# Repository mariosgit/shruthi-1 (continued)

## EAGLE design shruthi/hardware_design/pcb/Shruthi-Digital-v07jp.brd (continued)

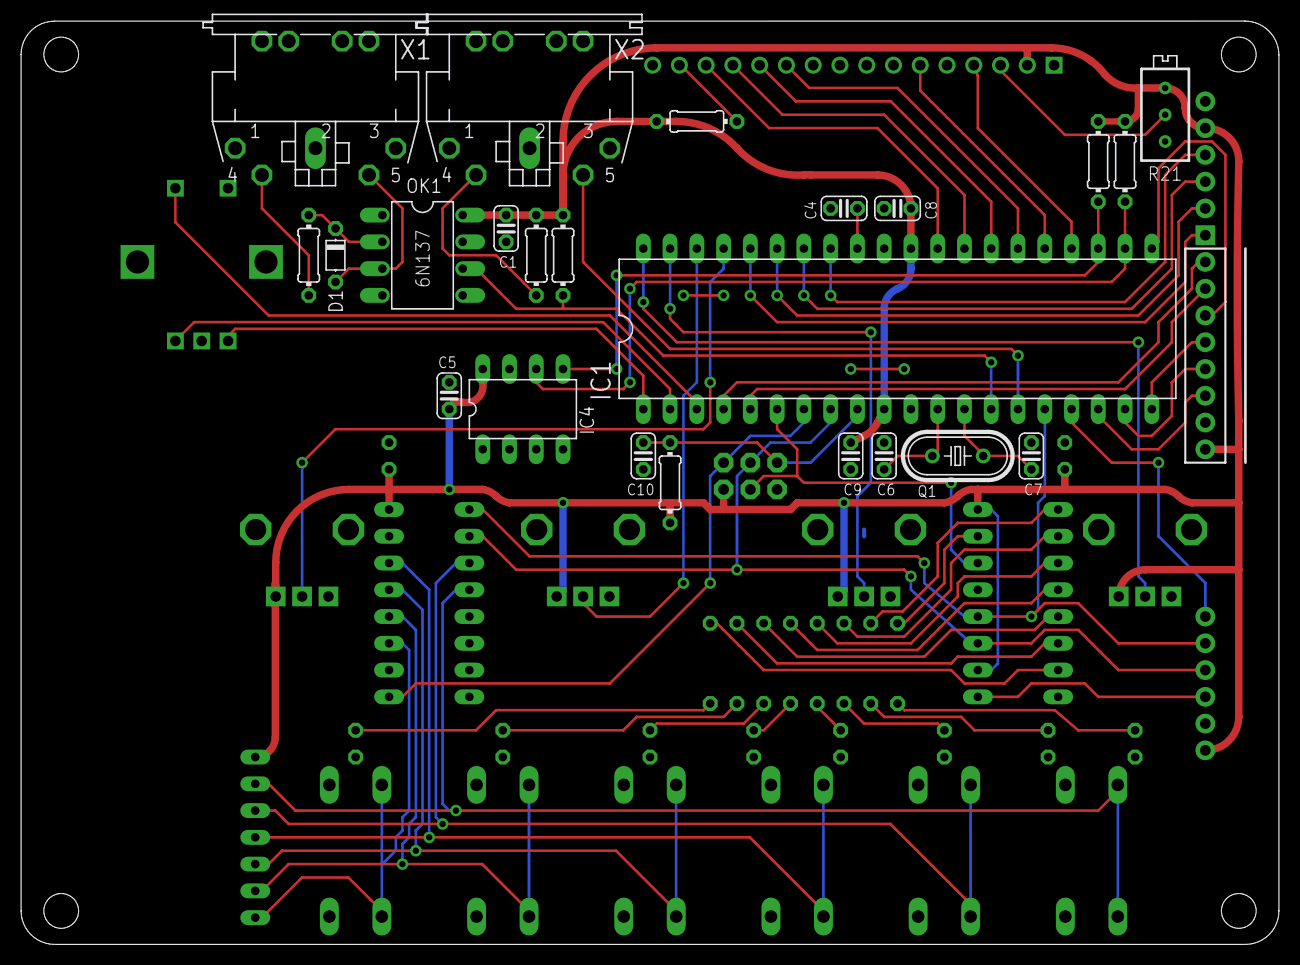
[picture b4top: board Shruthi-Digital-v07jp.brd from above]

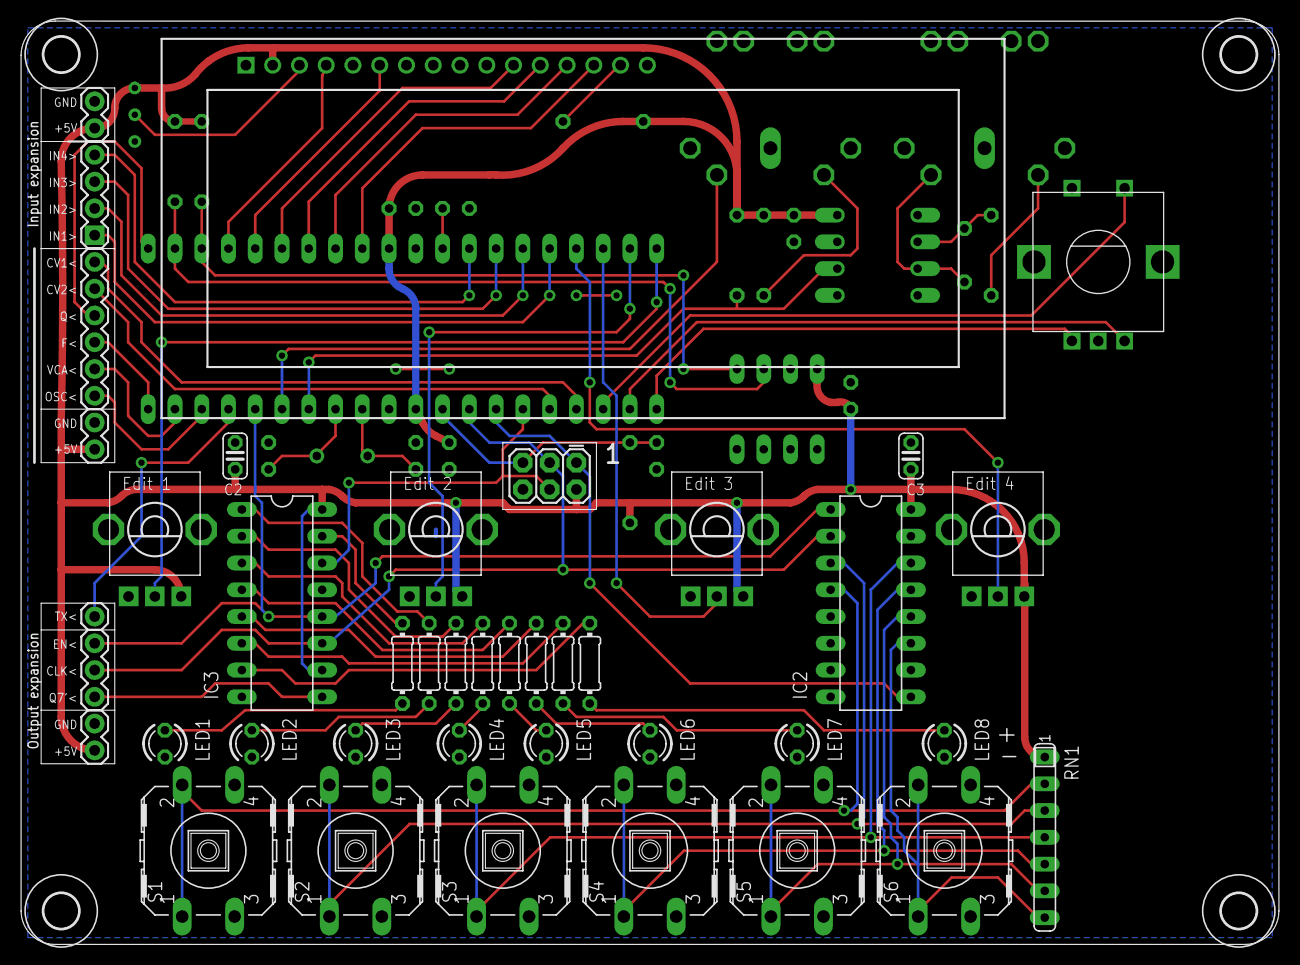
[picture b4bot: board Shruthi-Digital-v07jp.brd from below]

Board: 2 copper layers, 119.4 x 87.6 mm, 70 parts (46 on the bottom side), 67 nets.

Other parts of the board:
U$2, U$3, U$4, U$5: 3,3
U$6: MANGA_GIRL
U$7: MUTABLE_PROF

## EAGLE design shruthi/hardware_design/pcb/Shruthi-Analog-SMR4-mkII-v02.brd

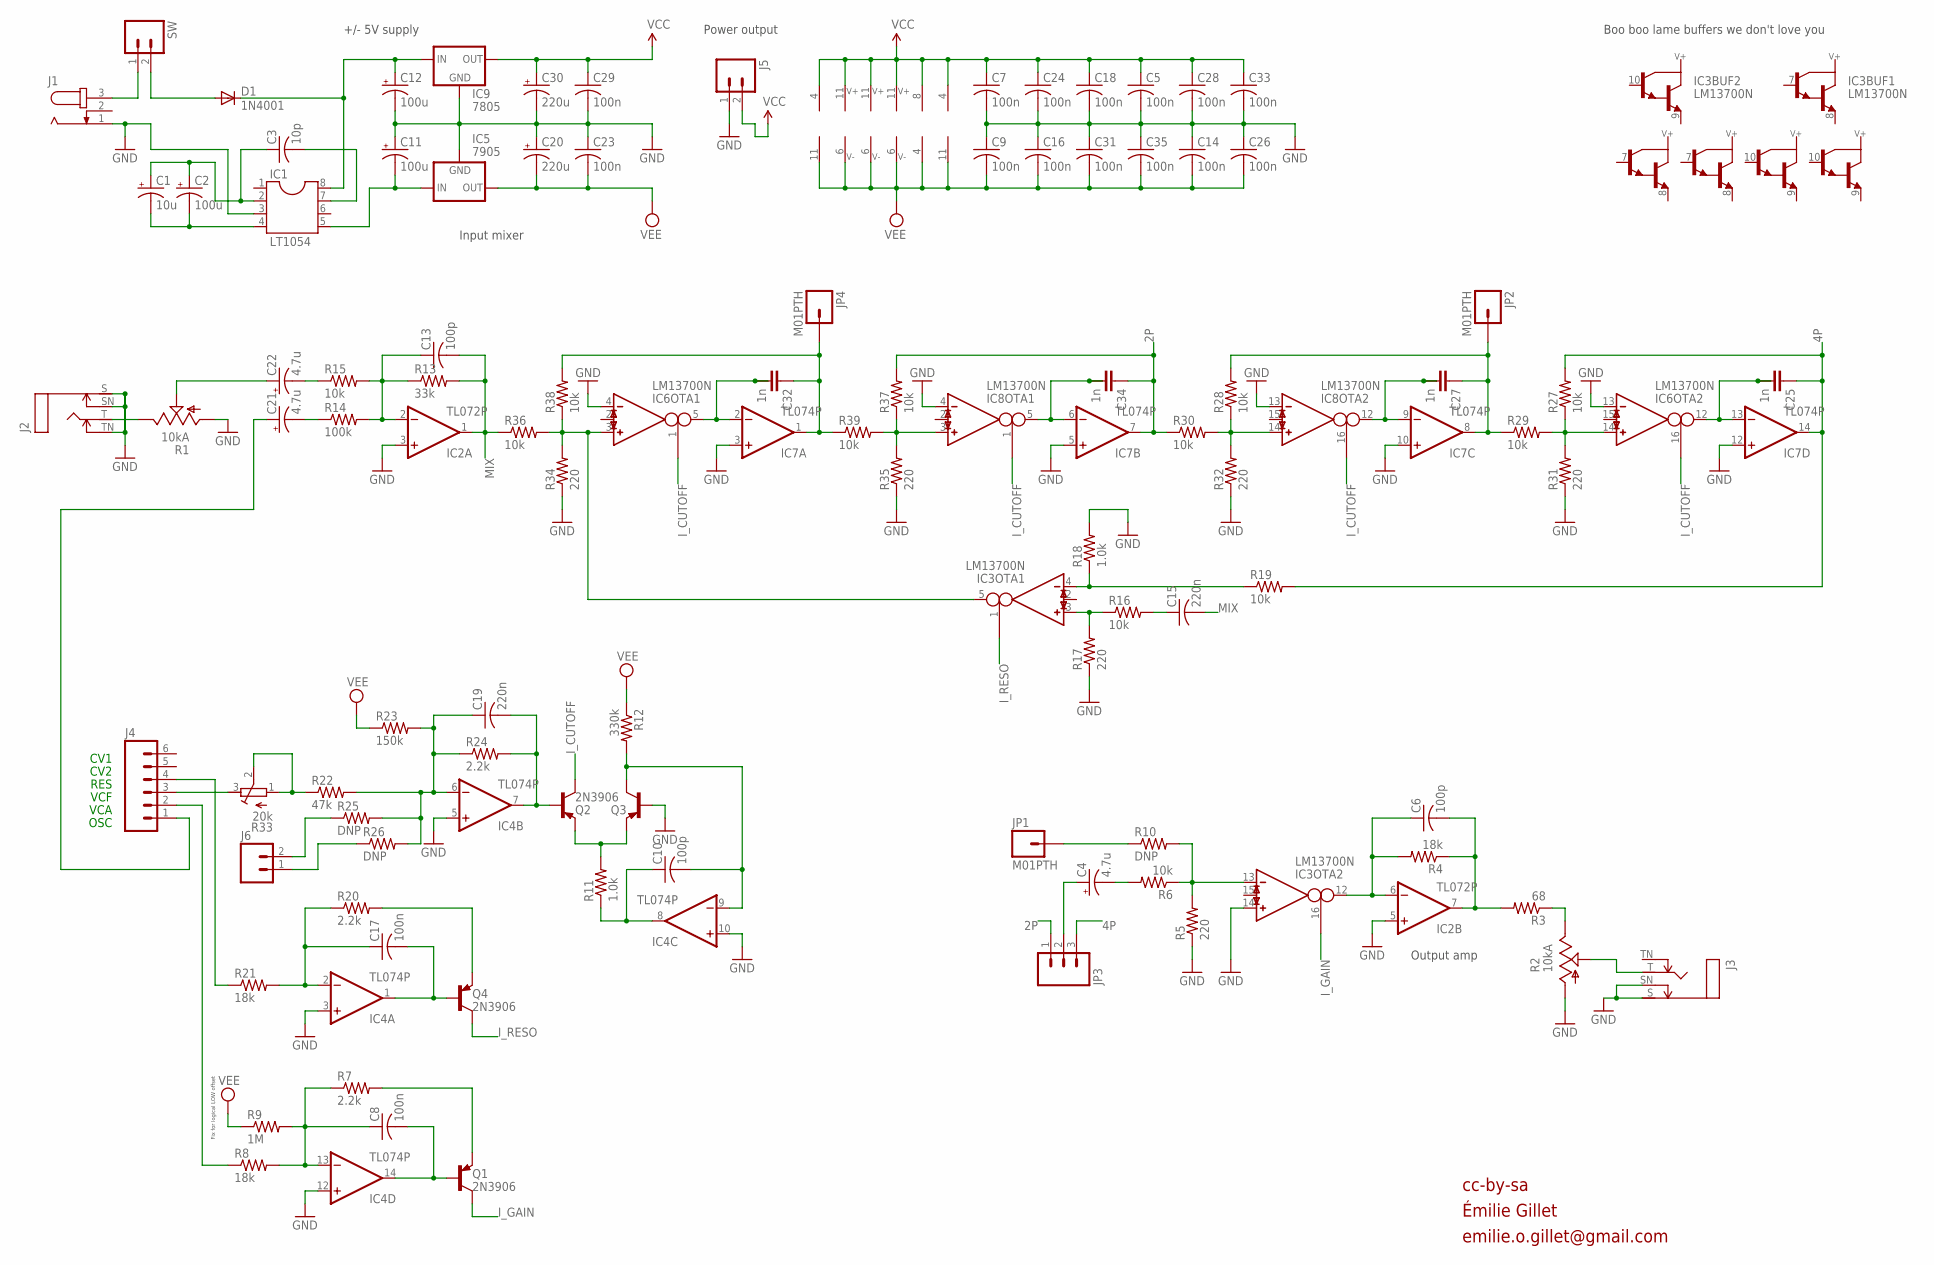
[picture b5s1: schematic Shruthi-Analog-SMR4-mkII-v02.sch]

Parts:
C1: 10u; E2,5-5
C2: 100u; E2,5-6
C3: 10p; C025-025X050
C4, C21, C22: 4.7u; E2,5-6
C5, C7, C8, C9, C14, C16, C17, C18, C23, C24, C26, C28, C29, C31, C33, C35: 100n; C025-025X050
C6, C10, C13: 100p; C025-025X050
C11, C12: 100u; E2,5-7
C15, C19: 220n; C025-025X050
C20, C30: 220u; E5-10,5
C25, C27, C32, C34: 1n; C2.5/5-2
D1: 1N4001; DO41-10
IC1: LT1054; DIL08
IC2: TL072P; DIL08
IC3, IC6, IC8: LM13700N; DIL16
IC4, IC7: TL074P; DIL14
IC5: 7905; 79XXS
IC9: 7805; 78XXS
J1: JACK-PLUG2; SPC4078_BIG_HOLES
J2, J3: MONOSWS; NMJ4HC-S
J4: M06SIP; 1X06
J5, J6: M02PTH; 1X02
JP1, JP2, JP4: M01PTH; 1X01
JP3: M03PTH; 1X03
Q1, Q2, Q3, Q4: 2N3906; TO92-
R1, R2: 10kA; CABLE_POT_6MM
R3: 68; 0204/7
R4, R8, R21: 18k; 0204/7
R5, R17, R31, R32, R34, R35: 220; 0204/7
R6, R15, R16, R19, R27, R28, R29, R30, R36, R37, R38, R39: 10k; 0204/7
R7, R20, R24: 2.2k; 0204/7
R9: 1M; 0204/7
R10, R25, R26: DNP; 0204V
R11, R18: 1.0k; 0204/7
R12: 330k; 0204/7
R13: 33k; 0204/7
R14: 100k; 0204/7
R22: 47k; 0204/7
R23: 150k; 0204/7
R33: 20k; RTRIM3296X
SW: M02PTH; 1X02

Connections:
2P: C34.1, IC7.7 (OUT), JP3.1, R30.1, R37.2
4P: C25.1, IC7.14 (OUT), JP3.3, R19.2, R27.2
GND: C5.2, C7.2, C9.1, C11.+, C12.-, C14.1, C16.1, C18.2, C20.+, C23.1, C24.2, C26.1, C28.2, C29.2, C30.-, C31.1, C33.2, C35.1, IC1.3, IC2.3 (+IN), IC2.5 (+IN), IC3.14 (IN_P), IC4.3 (+IN), IC4.5 (+IN), IC4.10 (+IN), IC4.12 (+IN), IC5.GND, IC6.4 (IN_N), IC6.13 (IN_N), IC7.3 (+IN), IC7.5 (+IN), IC7.10 (+IN), IC7.12 (+IN), IC8.4 (IN_N), IC8.13 (IN_N), IC9.GND, J1.1, J2.S, J2.SN, J2.TN, J3.S, J3.SN, J5.1, Q3.2 (B), R1.A, R2.A, R5.1, R17.1, R18.2, R31.1, R32.1, R34.1, R35.1
I_CUTOFF: IC6.1 (I_BIAS), IC6.16 (I_BIAS), IC8.1 (I_BIAS), IC8.16 (I_BIAS), Q2.1 (C)
I_GAIN: IC3.16 (I_BIAS), Q1.1 (C)
I_RESO: IC3.1 (I_BIAS), Q4.1 (C)
MIX: C13.2, C15.2, IC2.1 (OUT), R13.2, R36.1
unnamed: JP1.1, R10.1
unnamed: C19.2, IC4.7 (OUT), Q2.2 (B), R24.2
unnamed: R22.1, R33.1 (E), R33.2 (S)
unnamed: J4.3, R33.3 (A)
unnamed: C13.1, IC2.2 (-IN), R13.1, R14.2, R15.2
unnamed: Q2.3 (E), Q3.3 (E), R11.2
unnamed: C4.+, JP3.2
unnamed: C10.1, IC4.8 (OUT), R11.1
unnamed: C10.2, IC4.9 (-IN), Q3.1 (C), R12.2
unnamed: J4.4, R21.1
unnamed: IC3.5 (OUT), IC6.3 (IN_P), R34.2, R36.2, R38.1
unnamed: J3.T, R2.S
unnamed: C32.1, IC7.1 (OUT), JP4.1, R38.2, R39.1
unnamed: IC8.3 (IN_P), R35.2, R37.1, R39.2
unnamed: C4.-, R6.2
unnamed: J6.2, R25.1
unnamed: IC8.14 (IN_P), R28.1, R30.2, R32.2
unnamed: C15.1, R16.2
unnamed: J6.1, R26.1
unnamed: IC6.14 (IN_P), R27.1, R29.2, R31.2
unnamed: R2.E, R3.1
unnamed: C27.1, IC7.8 (OUT), JP2.1, R28.2, R29.1
unnamed: C32.2, C32.3, IC6.5 (OUT), IC7.2 (-IN)
unnamed: C34.2, C34.3, IC7.6 (-IN), IC8.5 (OUT)
unnamed: IC3.4 (IN_N), R18.1, R19.1
unnamed: C17.2, IC4.1 (OUT), Q4.2 (B)
unnamed: C8.2, IC4.14 (OUT), Q1.2 (B)
unnamed: IC3.3 (IN_P), R16.1, R17.2
unnamed: IC3.13 (IN_N), R5.2, R6.1, R10.2
unnamed: C21.+, J4.1
unnamed: C27.2, C27.3, IC7.9 (-IN), IC8.12 (OUT)
unnamed: C25.2, C25.3, IC6.12 (OUT), IC7.13 (-IN)
unnamed: J2.T, R1.E
unnamed: C21.-, R14.1
unnamed: C19.1, IC4.6 (-IN), R22.2, R23.2, R24.1, R25.2, R26.2
unnamed: J1.3, SW.1
unnamed: J4.2, R8.1
unnamed: C12.+, D1.C, IC1.8, IC9.IN
unnamed: C1.+, C2.+, C3.1, IC1.2
unnamed: C1.-, C2.-, IC1.4
unnamed: C3.2, IC1.7
unnamed: C8.1, IC4.13 (-IN), R7.1, R8.2, R9.2
unnamed: C17.1, IC4.2 (-IN), R20.1, R21.2
unnamed: C11.-, IC1.5, IC5.IN
unnamed: D1.A, SW.2
unnamed: Q4.3 (E), R20.2
unnamed: C6.2, IC2.7 (OUT), R3.2, R4.1
unnamed: C22.+, R1.S
unnamed: Q1.3 (E), R7.2
unnamed: C6.1, IC2.6 (-IN), IC3.12 (OUT), R4.2
unnamed: C22.-, R15.1
VCC: C5.1, C7.1, C18.1, C24.1, C28.1, C29.1, C30.+, C33.1, IC2.8 (V+), IC3.11 (V+), IC4.4 (V+), IC6.11 (V+), IC7.4 (V+), IC8.11 (V+), IC9.OUT, J5.2
VEE: C9.2, C14.2, C16.2, C20.-, C23.2, C26.2, C31.2, C35.2, IC2.4 (V-), IC3.6 (V-), IC4.11 (V-), IC5.OUT, IC6.6 (V-), IC7.11 (V-), IC8.6 (V-), R9.1, R12.1, R23.1

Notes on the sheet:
Power output
OSC
VCA
VCF
RES
cc-by-sa
Output amp
CV1
CV2
Input mixer
+/- 5V supply
Boo boo lame buffers we don't love you
Fix for logical LOW offset
Émilie Gillet
emilie.o.gillet@gmail.com

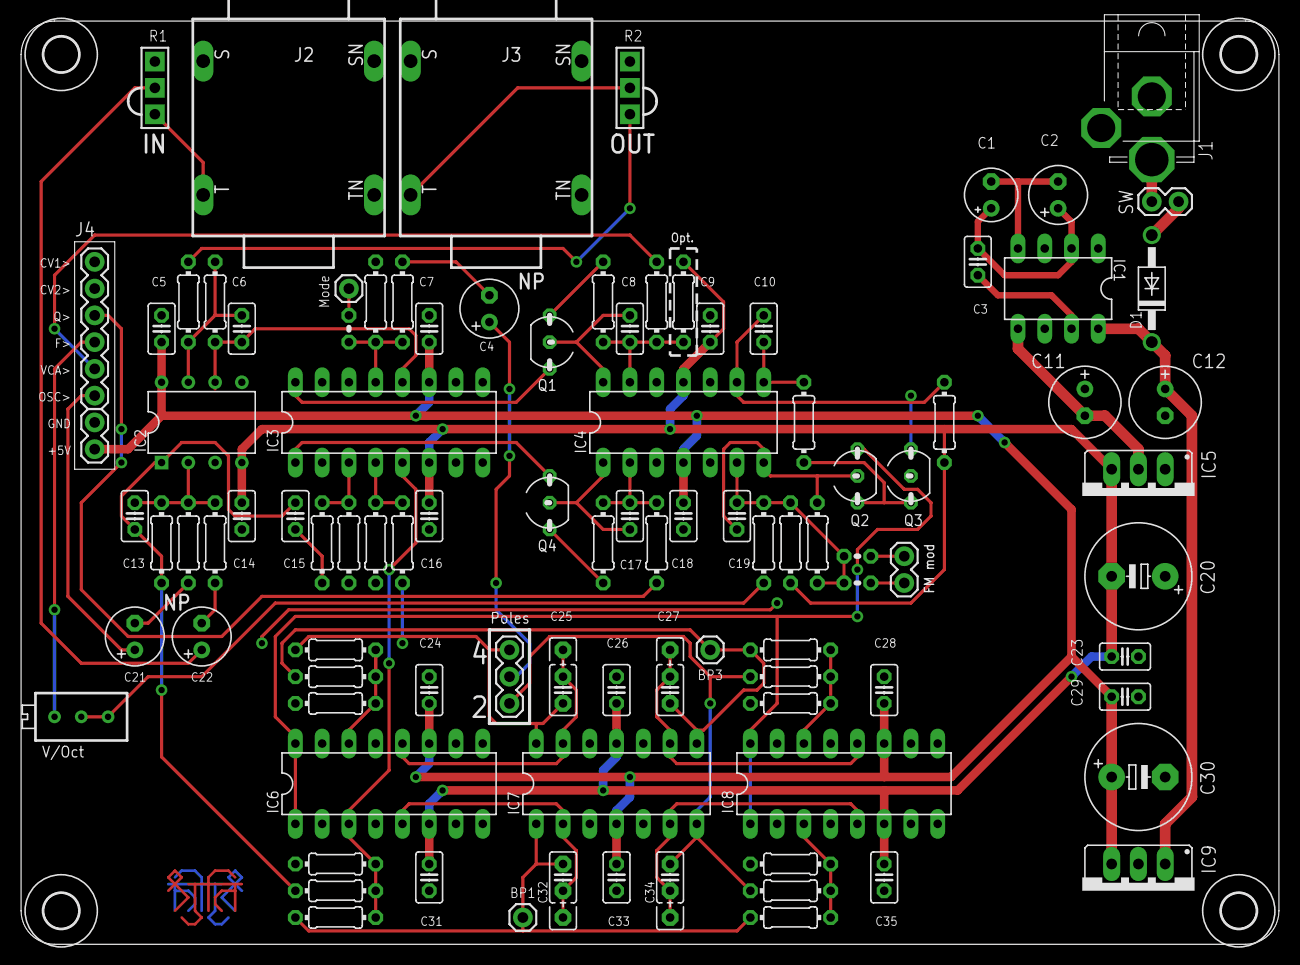
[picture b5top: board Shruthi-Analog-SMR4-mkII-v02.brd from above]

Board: 2 copper layers, 119.4 x 87.6 mm, 105 parts (0 on the bottom side), 60 nets.

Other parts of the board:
U$1, U$2, U$4, U$5: 3,3
U$3: V2_LOGO_SHRUTHI_ANALOG
U$6: V2_LOGO_DINGBAT1

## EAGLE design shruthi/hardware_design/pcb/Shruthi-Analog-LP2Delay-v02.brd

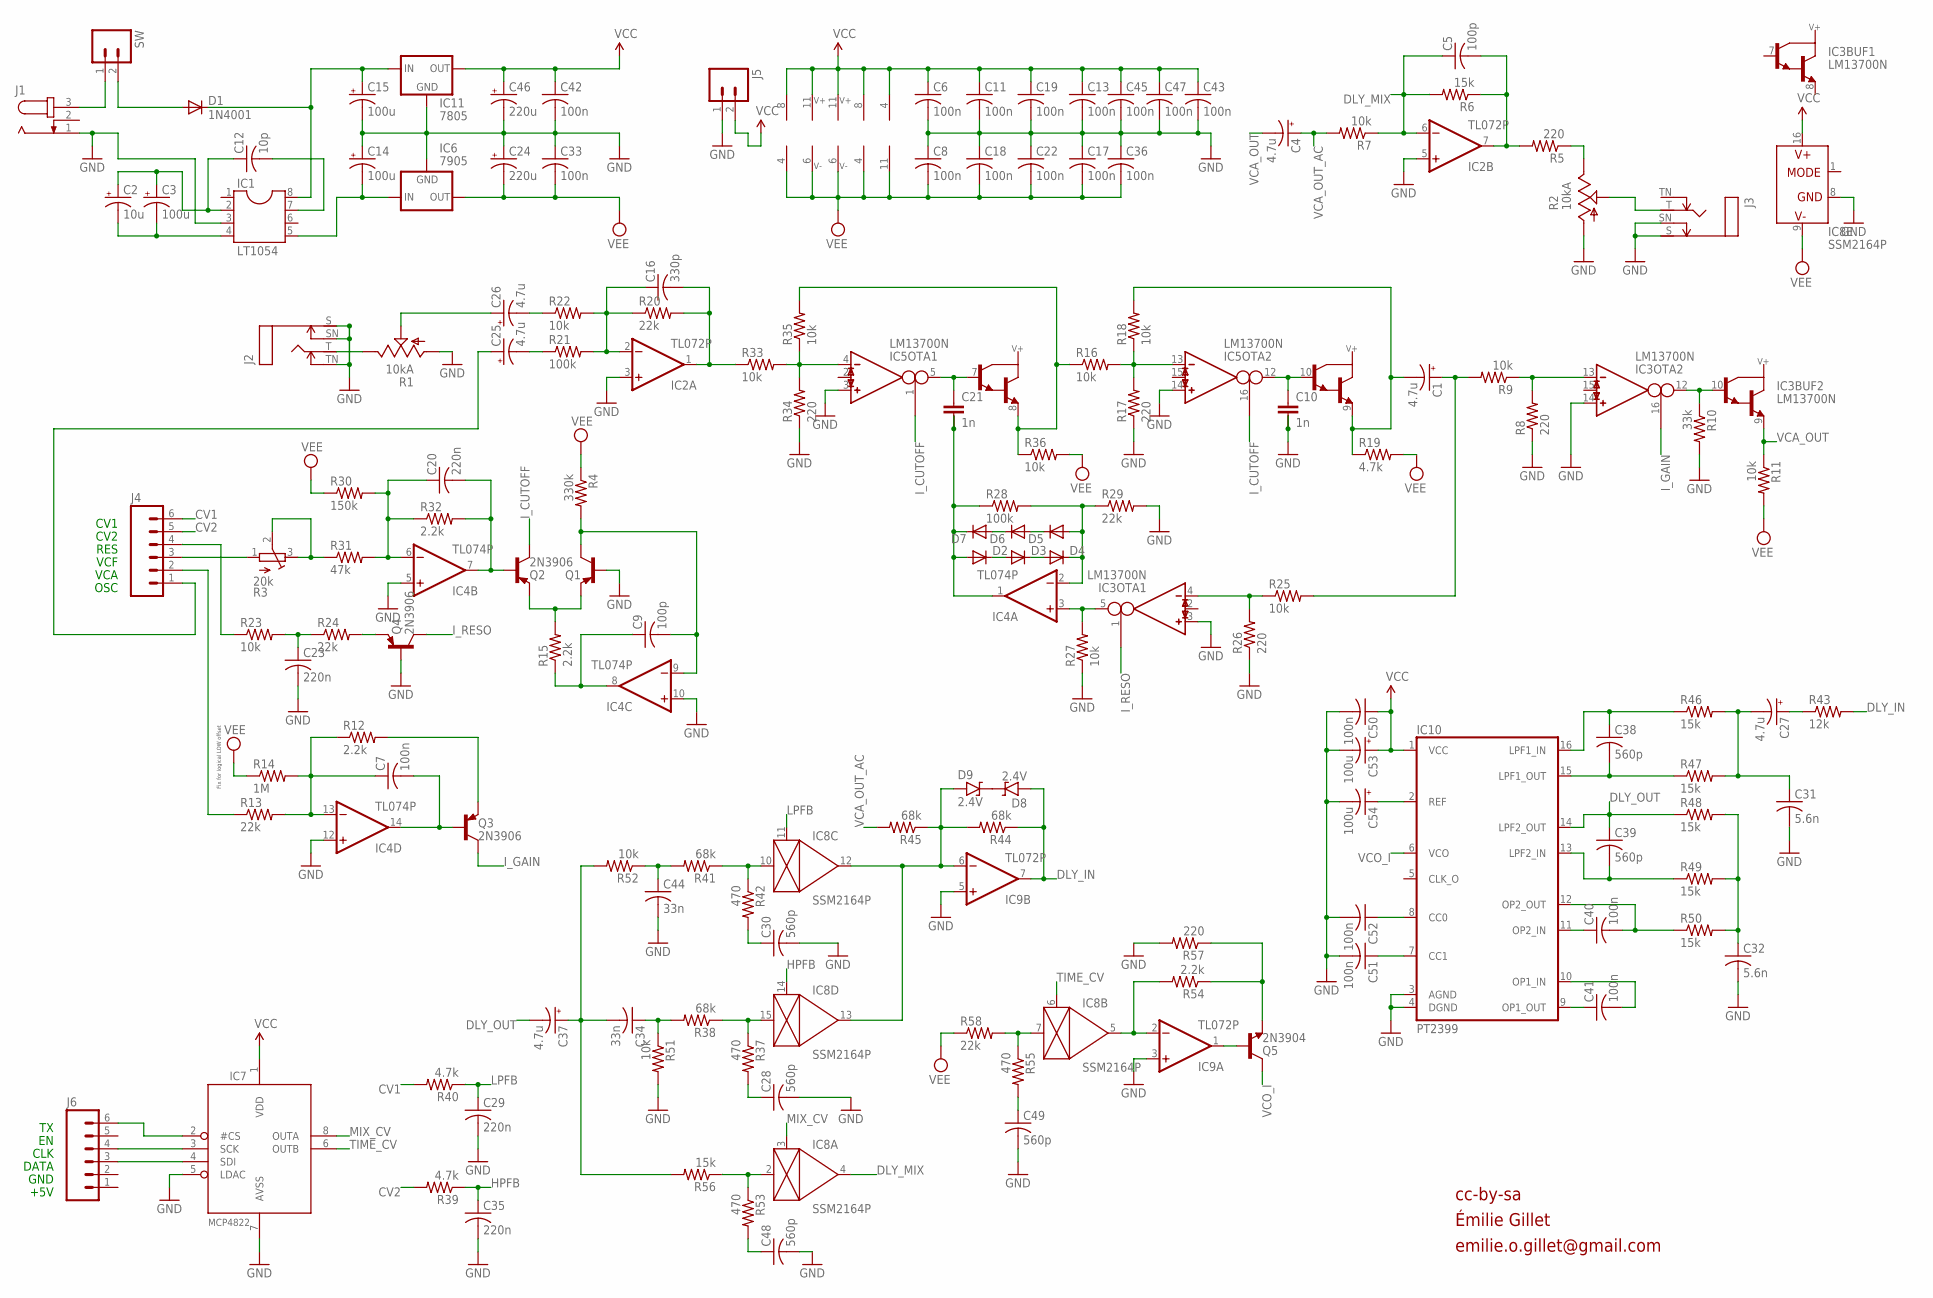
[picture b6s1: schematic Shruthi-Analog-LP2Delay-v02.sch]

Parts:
C1, C4, C25, C26, C27, C37: 4.7u; E2,5-6
C2: 10u; E2,5-5
C3: 100u; E2,5-6
C5, C9: 100p; C025-025X050
C6, C7, C8, C11, C13, C17, C18, C19, C22, C33, C36, C40, C41, C42, C43, C45, C47, C50, C51, C52: 100n; C025-025X050
C10, C21: 1n; C2.5/5-2
C12: 10p; C025-025X050
C14, C15, C53, C54: 100u; E2,5-7
C16: 330p; C025-025X050
C20, C23, C29, C35: 220n; C025-025X050
C24, C46: 220u; E5-10,5
C28, C30, C38, C39, C48, C49: 560p; C025-025X050
C31, C32: 5.6n; C025-025X050
C34, C44: 33n; C050-025X075
D1: 1N4001; DO41-10
D2, D3, D4, D5, D6, D7: DIODE-D-5; D-5
D8, D9: 2.4V; D-5
IC1: LT1054; DIL08
IC2, IC9: TL072P; DIL08
IC3, IC5: LM13700N; DIL16
IC4: TL074P; DIL14
IC6: 7905; 79XXS
IC7: MCP4822; DIL08
IC8: SSM2164P; DIL16
IC10: PT2399; DIL16
IC11: 7805; 78XXS
J1: JACK-PLUG2; SPC4078_BIG_HOLES
J2, J3: MONOSWS; NMJ4HC-S
J4, J6: M06SIP; 1X06
J5: M02PTH; 1X02
Q1, Q2, Q3, Q4: 2N3906; TO92-
Q5: 2N3904; TO92-
R1, R2: 10kA; CABLE_POT_6MM
R3: 20k; RTRIM3296X
R4: 330k; 0204/7
R5, R8, R17, R26, R34, R57: 220; 0204/7
R6, R46, R47, R48, R49, R50, R56: 15k; 0204/7
R7, R9, R11, R16, R18, R22, R23, R25, R27, R33, R35, R36, R51, R52: 10k; 0204/7
R10: 33k; 0204/7
R12, R15, R32, R54: 2.2k; 0204/7
R13, R20, R24, R29, R58: 22k; 0204/7
R14: 1M; 0204/7
R19, R39, R40: 4.7k; 0204/7
R21, R28: 100k; 0204/7
R30: 150k; 0204/7
R31: 47k; 0204/7
R37, R42, R53, R55: 470; 0204/7
R38, R41, R44, R45: 68k; 0204/7
R43: 12k; 0204/7
SW: M02PTH; 1X02

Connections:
2P: C1.-, IC5.9 (E), R18.2, R19.1
CAP_IN: D9.A, IC8.12 (OUT), IC8.13 (OUT), IC9.6 (-IN), R44.2, R45.1
CV1: J4.6, R40.2
CV2: J4.5, R39.2
DLY_IN: D8.A, IC9.7 (OUT), R43.2, R44.1
DLY_MIX: C5.1, IC2.6 (-IN), IC8.4 (OUT), R6.2, R7.1
DLY_OUT: C37.-, C39.1, IC10.14 (LPF2_OUT), R48.1
GND: C6.2, C8.1, C10.2, C10.3, C11.2, C13.2, C14.+, C15.-, C17.1, C18.1, C19.2, C22.1, C23.2, C24.+, C28.2, C29.2, C30.2, C31.2, C32.2, C33.1, C35.2, C36.1, C42.2, C43.2, C44.2, C45.2, C46.-, C47.2, C48.2, C49.2, C50.2, C51.2, C52.2, C53.-, C54.-, IC1.3, IC2.3 (+IN), IC2.5 (+IN), IC3.3 (IN_P), IC3.14 (IN_P), IC4.5 (+IN), IC4.10 (+IN), IC4.12 (+IN), IC5.3 (IN_P), IC5.14 (IN_P), IC6.GND, IC7.5 (LDAC), IC7.7 (AVSS), IC8.8 (GND), IC9.3 (+IN), IC9.5 (+IN), IC10.3 (AGND), IC10.4 (DGND), IC11.GND, J1.1, J2.S, J2.SN, J2.TN, J3.S, J3.SN, J5.1, Q1.2 (B), Q4.2 (B), R1.A, R2.A, R8.1, R10.2, R17.1, R26.1, R27.1, R29.2, R34.1, R51.2, R57.2
HPFB: C35.1, IC8.14 (CTRL), R39.1
I_CUTOFF: IC5.1 (I_BIAS), IC5.16 (I_BIAS), Q2.1 (C)
I_GAIN: IC3.16 (I_BIAS), Q3.1 (C)
I_RESO: IC3.1 (I_BIAS), Q4.1 (C)
LPFB: C29.1, IC8.11 (CTRL), R40.1
MIX: C16.2, IC2.1 (OUT), R20.2, R33.1
MIX_CV: IC7.8 (OUTA), IC8.3 (CTRL)
unnamed: IC3.5 (OUT), IC4.3 (+IN), R27.2
unnamed: C20.2, IC4.7 (OUT), Q2.2 (B), R32.2
unnamed: R3.2 (S), R3.3 (A), R31.1
unnamed: J4.3, R3.1 (E)
unnamed: C28.1, R37.2
unnamed: C16.1, IC2.2 (-IN), R20.1, R21.2, R22.2
unnamed: Q1.3 (E), Q2.3 (E), R15.2
unnamed: D4.C, D5.A, IC4.2 (-IN), R28.2, R29.1
unnamed: C9.1, IC4.8 (OUT), R15.1
unnamed: C9.2, IC4.9 (-IN), Q1.1 (C), R4.2
unnamed: J4.4, R23.1
unnamed: Q4.3 (E), R24.2
unnamed: J3.T, R2.S
unnamed: C23.1, R23.2, R24.1
unnamed: IC5.13 (IN_N), R16.2, R17.2, R18.1
unnamed: C30.1, R42.2
unnamed: C1.+, R9.2, R25.2
unnamed: IC5.8 (E), R16.1, R35.2, R36.1
unnamed: C10.1, IC5.10 (B), IC5.12 (OUT)
unnamed: IC8.10 (IN), R41.1, R42.1
unnamed: IC8.15 (IN), R37.1, R38.1
unnamed: IC5.4 (IN_N), R33.2, R34.2, R35.1
unnamed: D5.C, D6.A
unnamed: R2.E, R5.1
unnamed: D6.C, D7.A
unnamed: C21.1, IC5.5 (OUT), IC5.7 (B)
unnamed: D2.C, D3.A
unnamed: IC3.4 (IN_N), R25.1, R26.2
unnamed: D3.C, D4.A
unnamed: C7.2, IC4.14 (OUT), Q3.2 (B)
unnamed: C41.1, IC10.9 (OP1_OUT)
unnamed: IC3.10 (B), IC3.12 (OUT), R10.1
unnamed: IC3.13 (IN_N), R8.2, R9.1
unnamed: C25.+, J4.1
unnamed: C51.1, IC10.7 (CC1)
unnamed: C52.1, IC10.8 (CC0)
unnamed: J2.T, R1.E
unnamed: C25.-, R21.1
unnamed: C20.1, IC4.6 (-IN), R30.2, R31.2, R32.1
unnamed: C27.+, R43.1
unnamed: C54.+, IC10.2 (REF)
unnamed: C41.2, IC10.10 (OP1_IN)
unnamed: J1.3, SW.1
unnamed: J4.2, R13.1
unnamed: C15.+, D1.C, IC1.8, IC11.IN
unnamed: C2.+, C3.+, C12.1, IC1.2
unnamed: C2.-, C3.-, IC1.4
unnamed: C12.2, IC1.7
unnamed: C40.1, IC10.11 (OP2_IN)
unnamed: C7.1, IC4.13 (-IN), R12.1, R13.2, R14.2
unnamed: C40.2, IC10.12 (OP2_OUT), R50.1
unnamed: D8.C, D9.C
unnamed: C38.2, IC10.15 (LPF1_OUT), R47.1
unnamed: C14.-, IC1.5, IC6.IN
unnamed: D1.A, SW.2
unnamed: C32.1, R48.2, R49.2, R50.2
unnamed: C39.2, IC10.13 (LPF2_IN), R49.1
unnamed: C38.1, IC10.16 (LPF1_IN), R46.1
unnamed: C5.2, IC2.7 (OUT), R5.2, R6.1
unnamed: C27.-, C31.1, R46.2, R47.2
unnamed: C21.2, C21.3, D2.A, D7.C, IC4.1 (OUT), R28.1
unnamed: C26.+, R1.S
unnamed: Q3.3 (E), R12.2
unnamed: IC9.1 (OUT), Q5.2 (B)
unnamed: C48.1, R53.2
unnamed: C26.-, R22.1
unnamed: IC8.2 (IN), R53.1, R56.1
unnamed: C34.1, R38.2, R51.1
unnamed: C44.1, R41.2, R52.1
unnamed: C34.2, C37.+, R52.2, R56.2
unnamed: IC8.5 (OUT), IC9.2 (-IN), R54.2
unnamed: Q5.3 (E), R54.1, R57.1
unnamed: IC7.2 (#CS), J6.6
unnamed: IC7.3 (SCK), J6.4
unnamed: IC7.4 (SDI), J6.3
unnamed: C49.1, R55.2
unnamed: IC8.7 (IN), R55.1, R58.2
TIME_CV: IC7.6 (OUTB), IC8.6 (CTRL)
VCA_OUT: C4.-, IC3.9 (E), R11.1
VCA_OUT_AC: C4.+, R7.2, R45.2
VCC: C6.1, C11.1, C13.1, C19.1, C42.1, C43.1, C45.1, C46.+, C47.1, C50.1, C53.+, IC2.8 (V+), IC3.11 (V+), IC4.4 (V+), IC5.11 (V+), IC7.1 (VDD), IC8.16 (V+), IC9.8 (V+), IC10.1 (VCC), IC11.OUT, J5.2
VCO_I: IC10.6 (VCO), Q5.1 (C)
VEE: C8.2, C17.2, C18.2, C22.2, C24.-, C33.2, C36.2, IC2.4 (V-), IC3.6 (V-), IC4.11 (V-), IC5.6 (V-), IC6.OUT, IC8.9 (V-), IC9.4 (V-), R4.1, R11.2, R14.1, R19.2, R30.1, R36.2, R58.1

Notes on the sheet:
OSC
VCA
VCF
RES
cc-by-sa
CV1
CV2
Fix for logical LOW offset
+5V
GND
DATA
CLK
Émilie Gillet
emilie.o.gillet@gmail.com

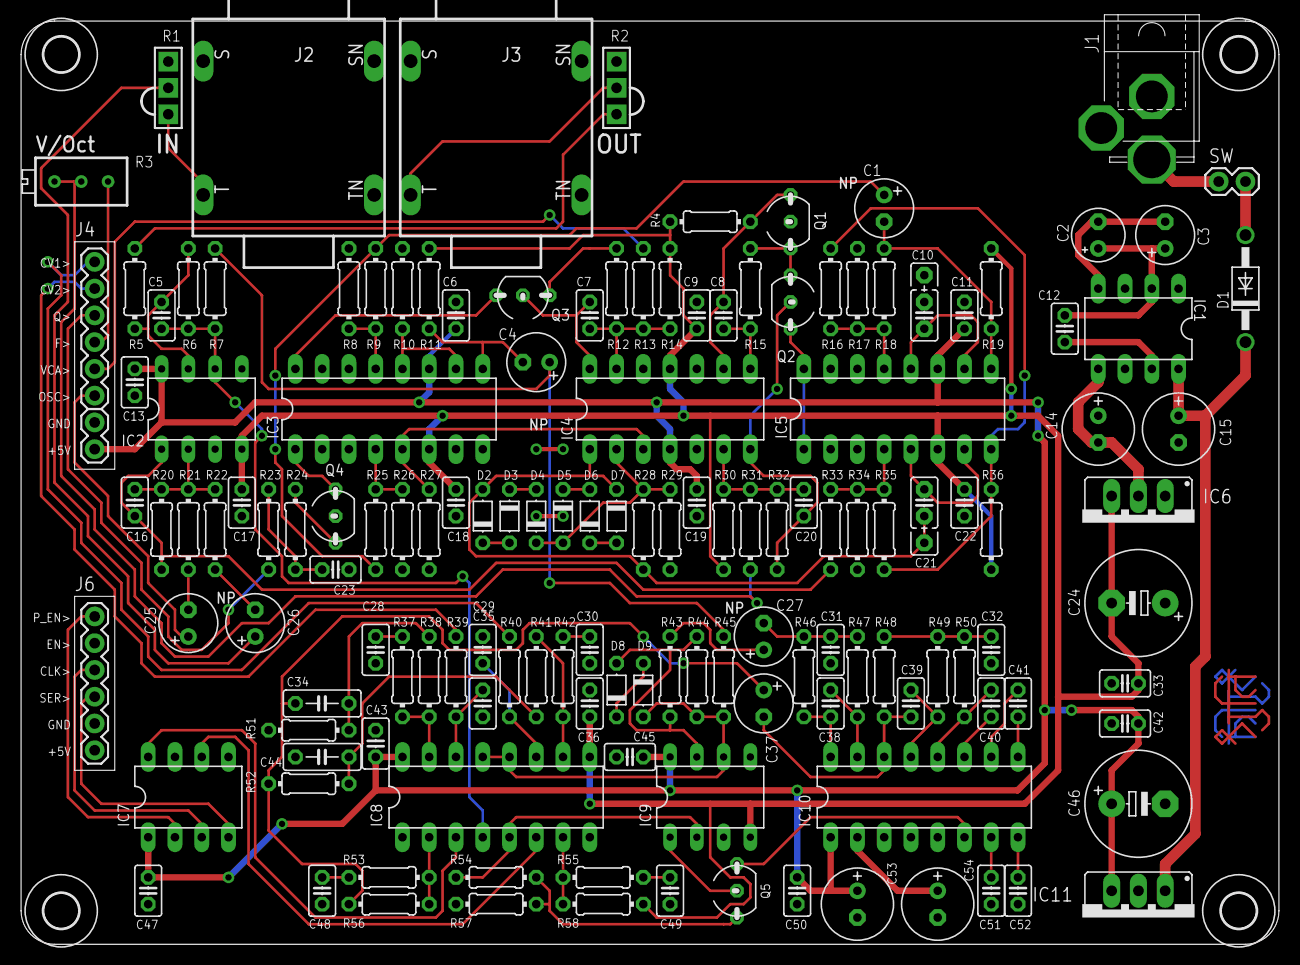
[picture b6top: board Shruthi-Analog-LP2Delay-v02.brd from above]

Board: 2 copper layers, 119.4 x 87.6 mm, 149 parts (0 on the bottom side), 98 nets.

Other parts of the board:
U$1, U$2, U$3, U$4: 3,3
U$5: MUTABLE_PROF

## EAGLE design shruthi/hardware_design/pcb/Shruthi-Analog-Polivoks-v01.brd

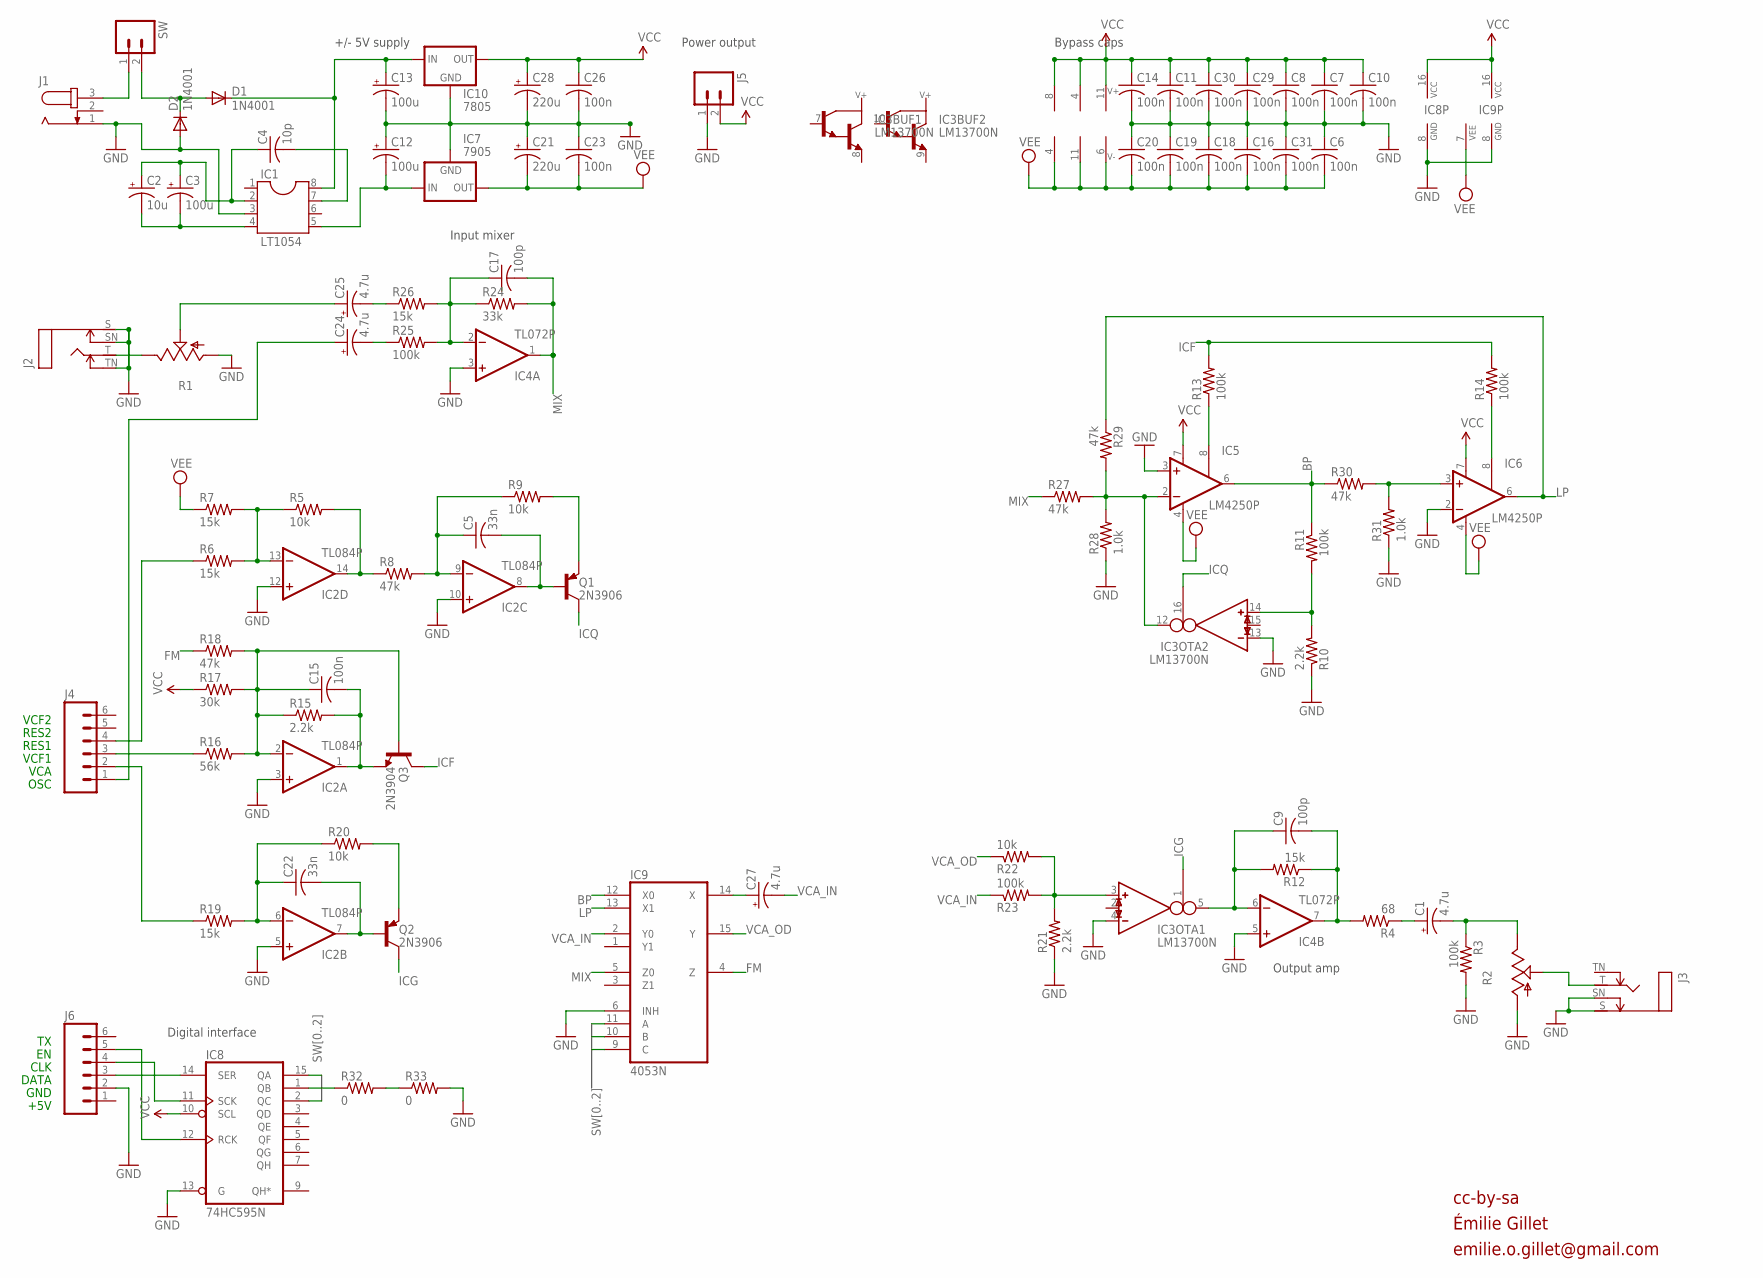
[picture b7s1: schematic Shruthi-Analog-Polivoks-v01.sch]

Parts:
C1, C24, C25, C27: 4.7u; E2,5-6
C2: 10u; E2,5-5
C3: 100u; E2,5-6
C4: 10p; C025-025X050
C5, C22: 33n; C050-025X075
C6, C7, C8, C10, C11, C14, C15, C16, C18, C19, C20, C23, C26, C29, C30, C31: 100n; C025-025X050
C9, C17: 100p; C025-025X050
C12, C13: 100u; E2,5-7
C21, C28: 220u; E5-10,5
D1, D2: 1N4001; DO41-10
IC1: LT1054; DIL08
IC2: TL084P; DIL14
IC3: LM13700N; DIL16
IC4: TL072P; DIL08
IC5, IC6: LM4250P; DIL08
IC7: 7905; 79XXS
IC8: 74HC595N; DIL16
IC9: 4053N; DIL16
IC10: 7805; 78XXS
J1: JACK-PLUG2; SPC4078_BIG_HOLES
J2, J3: MONOSWS; NMJ4HC-S
J4, J6: M06SIP; 1X06
J5: M02PTH; 1X02
Q1, Q2: 2N3906; TO92-
Q3: 2N3904; TO92-
R1, R2: POT_USCABLED; CABLE_POT_6MM
R3, R11, R13, R14, R23, R25: 100k; 0204/7
R4: 68; 0204/7
R5, R9, R20, R22: 10k; 0204/7
R6, R7, R12, R19, R26: 15k; 0204/7
R8, R18, R27, R29, R30: 47k; 0204/7
R10, R15, R21: 2.2k; 0204/7
R16: 56k; 0204/7
R17: 30k; 0204/7
R24: 33k; 0204/7
R28, R31: 1.0k; 0204/7
R32, R33: 0; 0204V
SW: M02PTH; 1X02

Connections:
BP: IC5.6 (OUT), IC9.12 (X0), R11.1, R30.1
FM: IC9.4 (Z), R18.1
FREQ1: C15.2, IC2.1 (OUT), Q3.3 (E), R15.2
FREQ2: C5.2, IC2.8 (OUT), Q1.2 (B)
GND: C6.1, C7.2, C8.2, C10.2, C11.2, C12.+, C13.-, C14.2, C16.1, C18.1, C19.1, C20.1, C21.+, C23.1, C26.2, C28.-, C29.2, C30.2, C31.1, D2.A, IC1.3, IC2.3 (+IN), IC2.5 (+IN), IC2.10 (+IN), IC2.12 (+IN), IC3.4 (IN_N), IC3.13 (IN_N), IC4.3 (+IN), IC4.5 (+IN), IC5.3 (+IN), IC6.2 (-IN), IC7.GND, IC8.8 (GND), IC8.13 (G), IC9.6 (INH), IC9.8 (GND), IC10.GND, J1.1, J2.S, J2.SN, J2.TN, J3.S, J3.SN, J5.1, J6.2, R1.A, R2.A, R3.2, R10.1, R21.1, R28.1, R31.1, R33.2
ICF: Q3.1 (C), R13.2, R14.2
ICG: IC3.1 (I_BIAS), Q2.1 (C)
ICQ: IC3.16 (I_BIAS), Q1.1 (C)
LP: IC6.6 (OUT), IC9.13 (X1), R29.1
MIX: C17.2, IC4.1 (OUT), IC9.5 (Z0), R24.2, R27.1
unnamed: C2.+, C3.+, C4.1, IC1.2
unnamed: J4.4, R6.1
unnamed: J1.3, SW.1
unnamed: C13.+, D1.C, IC1.8, IC10.IN
unnamed: C2.-, C3.-, IC1.4
unnamed: C17.1, IC4.2 (-IN), R24.1, R25.2, R26.2
unnamed: C22.1, IC2.6 (-IN), R19.2, R20.1
unnamed: C5.1, IC2.9 (-IN), R8.2, R9.1
unnamed: Q2.3 (E), R20.2
unnamed: Q1.3 (E), R9.2
unnamed: IC3.12 (OUT), IC5.2 (-IN), R27.2, R28.2, R29.2
unnamed: IC8.12 (RCK), J6.5
unnamed: IC8.14 (SER), J6.3
unnamed: IC8.11 (SCK), J6.4
unnamed: C27.+, IC9.14 (X)
unnamed: IC3.3 (IN_P), R21.2, R22.2, R23.2
unnamed: IC3.14 (IN_P), R10.2, R11.2
unnamed: IC6.3 (+IN), R30.2, R31.2
unnamed: J4.2, R19.1
unnamed: IC2.13 (-IN), R5.1, R6.2, R7.2
unnamed: IC5.8 (ISET), R13.1
unnamed: IC6.8 (ISET), R14.1
unnamed: C1.+, R4.1
unnamed: R32.2, R33.1
unnamed: IC2.14 (OUT), R5.2, R8.1
unnamed: C1.-, R2.E, R3.1
unnamed: C24.+, J4.1
unnamed: C4.2, IC1.7
unnamed: J2.T, R1.E
unnamed: C24.-, R25.1
unnamed: C15.1, IC2.2 (-IN), Q3.2 (B), R15.1, R16.2, R17.2, R18.2
unnamed: J4.3, R16.1
unnamed: J3.T, R2.S
unnamed: C12.-, IC1.5, IC7.IN
unnamed: D1.A, D2.C, SW.2
unnamed: C9.2, IC4.7 (OUT), R4.2, R12.1
unnamed: C25.+, R1.S
unnamed: C9.1, IC3.5 (OUT), IC4.6 (-IN), R12.2
unnamed: C25.-, R26.1
SW0: IC8.15 (QA), IC9.9 (C)
SW1: IC8.1 (QB), IC9.10 (B), R32.1
SW2: IC8.2 (QC), IC9.11 (A)
VCA_IN: C27.-, IC9.2 (Y0), R23.1
VCA_OD: IC9.15 (Y), R22.1
VCC: C7.1, C8.1, C10.1, C11.1, C14.1, C26.1, C28.+, C29.1, C30.1, IC2.4 (V+), IC3.11 (V+), IC4.8 (V+), IC5.7 (V+), IC6.7 (V+), IC8.10 (SCL), IC8.16 (VCC), IC9.16 (VCC), IC10.OUT, J5.2, R17.1
VEE: C6.2, C16.2, C18.2, C19.2, C20.2, C21.-, C23.2, C31.2, IC2.11 (V-), IC3.6 (V-), IC4.4 (V-), IC5.4 (V-), IC6.4 (V-), IC7.OUT, IC9.7 (VEE), R7.1
X: C22.2, IC2.7 (OUT), Q2.2 (B)

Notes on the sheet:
Power output
OSC
VCA
VCF1
RES1
Input mixer
cc-by-sa
+/- 5V supply
Bypass caps
Output amp
VCF2
RES2
+5V
GND
DATA
CLK
Digital interface
Émilie Gillet
emilie.o.gillet@gmail.com

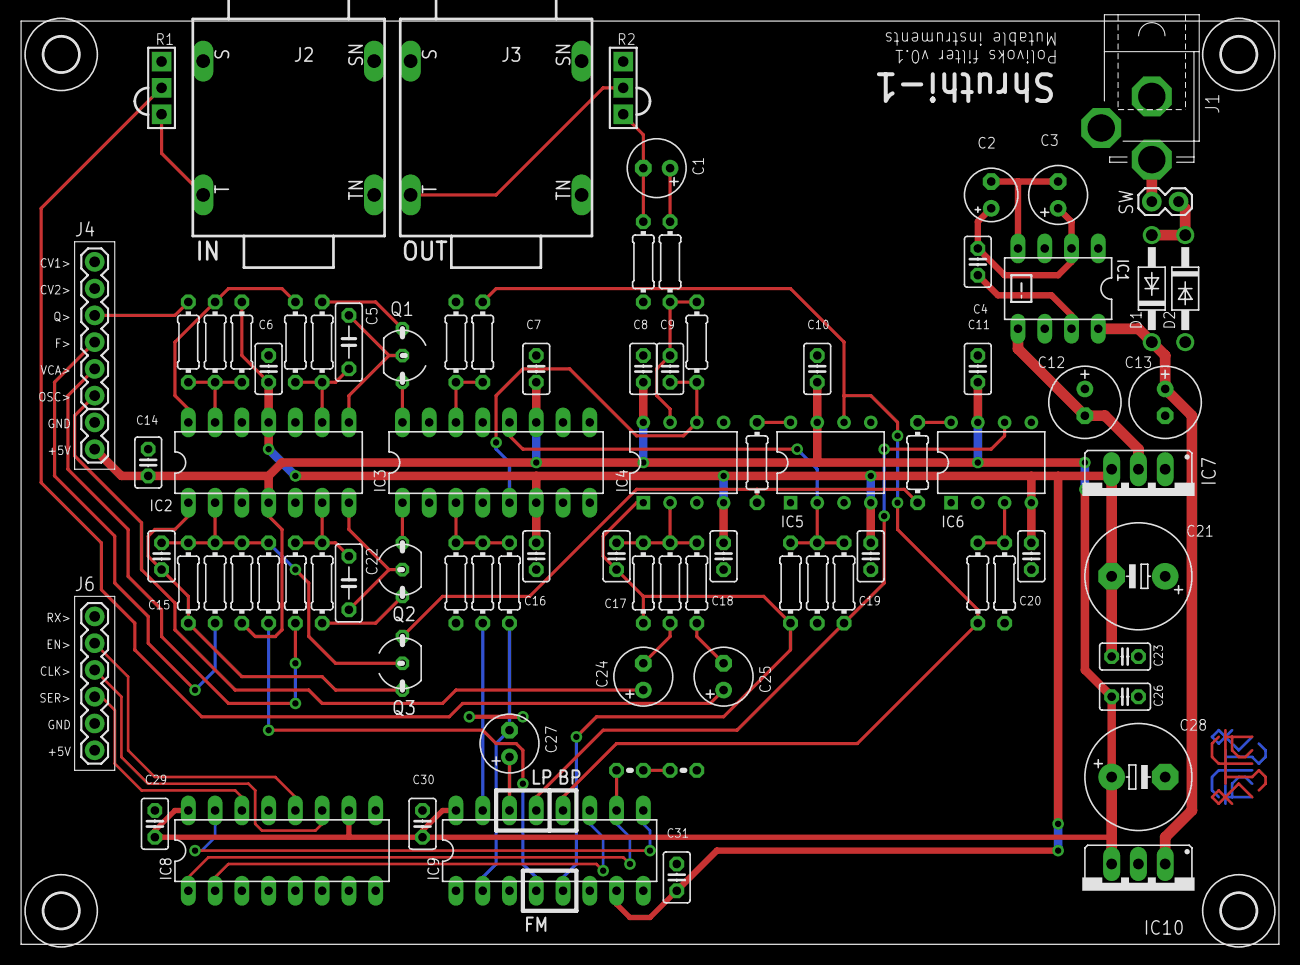
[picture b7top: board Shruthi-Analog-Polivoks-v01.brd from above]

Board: 2 copper layers, 119.4 x 87.6 mm, 92 parts (0 on the bottom side), 57 nets.

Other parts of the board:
$$U$4: 3,3
U$1, U$2, U$3: 3,3
U$4: ANUSHKA
U$5: SHRUTHI_LOGO_RUSSIAN

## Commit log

2024-07-02 saved as eagle 9.x (xml), KiCADable.
2024-07-02 Added 2 kicad conversions
